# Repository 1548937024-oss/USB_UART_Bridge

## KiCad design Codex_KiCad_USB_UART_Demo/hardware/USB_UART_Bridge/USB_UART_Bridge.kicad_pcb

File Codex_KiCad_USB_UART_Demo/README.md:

# Codex + KiCad USB-UART 演示

本目录用于建立一套可复现的 Codex 驱动 PCB 开发流程。演示电路采用
`CH343G`，实现隔离型 USB 2.0 转 3.3 V UART。

整个流程把需求、设计意图、脚本和 KiCad 工程文件都作为可版本控制的
工程资料。允许使用图形界面完成必要操作，但每个发布关口都必须能够通过
命令行重复执行。

## 当前进度

- P0 环境锁定：已完成。
- P1 需求锁定：已完成。
- P2 架构与选型：已完成。
- P3 原理图：已完成 `rev 0.2`，采用 A4 层次化图纸，已按 §10 统一网络命名、增加模块边框、
  器件注释、修订表和 `TP1-TP4` 测试点；ERC 为 0 错误、0 警告，栅格、标签间距和
  A4 边界检查均已通过，已重新生成网表、BOM 和 PDF。
- P4 PCB 设置与布局：已完成初版布局，生成 55 x 32 mm、2 mm 圆角、2 层 PCB、
  37 个封装（含 4 个 M2 安装孔）和 2 个隔离禁布区；J1 位于最左侧，
  J2/JP1 使用 2.54 mm 卧式弯针，在最右侧上下并排并缩小间隙，连接器本体伸出板外；
  四个 M2 安装孔布置在板卡四角；
  PS1 的 1/2 脚与 3/4 脚分置隔离区两侧，中间设置槽；U2 紧邻 J1 放置。
- P5 布线：已完成脚本化布线，DRC 为 0 个未连接项；保留 4 条 J1
  封装内部孔间距错误和连接器有意伸出板边产生的丝印警告。

当前原理图的网络标签优先落在实际连接走线上，不再为每个引脚固定拉出
`7.62 mm` 引线。同一局部区域内的同网引脚使用短实线连接；跨区域或会形成
交叉的连接使用同名网络标签。器件按照 USB 输入、桥接、隔离和输出四个功能区
排列，并通过旋转调整电流方向和走线方向。

原理图中的器件原点、全部引脚位置、走线端点、网络标签和 no-connect 均
必须落在 KiCad 默认的 `1.27 mm` 栅格上。生成脚本和验证脚本都会执行该检查。

原理图分为三个层次：

- 顶层 `USB_UART_Bridge.kicad_sch`：放置 USB-C、USB ESD、CC 下拉、UART 接口和
  VOUT 选择，并连接外部电气网络；USB 功能块整体位于左下区域。
- `Power.kicad_sch`：放置保险丝、隔离电源、隔离侧 LDO 及其去耦。
- `Communicate.kicad_sch`：放置 USB-UART 桥、数字隔离器和辅助状态电路。

跨图纸信号使用层次标签和图纸引脚连接。电源网络使用 `power` 库中的电源符号，
不使用普通网络标签。

`PWR_FLAG` 用于告诉 ERC 某些电源或地网络由外部连接器直接提供，避免把
USB-C、排针等无源接口误报为“电源没有驱动源”。它不是电源器件，也不会改变
`PWR_5V_RAW`、`PWR_5V_USB`、`PWR_VOUT_ISO`、`GND` 之间的实际连接关系。

## 版本记录

| Rev | Date | Author | Changes |
| --- | --- | --- | --- |
| 0.2 | 2026-09-19 | Codex | 修复 ERC 告警和错误，收紧 `pin_to_pin` 与单端全局标签检查，修正标签间距和 A4 边界问题 |
| 0.1 | 2026-09-14 | Codex | 初始层次化隔离 USB-UART 原理图、ERC 与制造输出流程 |

## 采购与成本

- `procurement/USB_UART_Bridge_Procurement_BOM.xlsx`：采购 BOM、预算单价、询价输入、
  采购数量、备件率和成本汇总。
- `procurement/USB_UART_Bridge_Procurement_BOM.csv`：可导入采购系统或继续编辑的
  简化版 BOM。

当前成本表按 5 片首版样机、默认 10% 备件率估算。表中单价用于提前备料和数量级
评估，实际下单前应把供应商报价填入“实际报价”列，并复核库存、MOQ 和交期。

原理图使用工程内的 `AD_Style_A4.kicad_wks` 图纸模板。该模板采用 A4 横向
ISO 5457/ISO 7200 compact 分区边框和右下工程标题栏，整体观感接近 AD
原理图的工业图纸样式。KiCad 图形界面和 `kicad-cli` PDF 导出均引用同一模板。

非电源网络会按曼哈顿距离建立最小生成树，并自动选择尽量短的直角走线把同网
引脚实际连接起来；电源网络继续通过电源符号建立全局连接。

生成流程最后会调用 `kicad-cli sch upgrade --force`，确保三张原理图文件头
始终升级为当前安装的 KiCad 10.0 格式。

## 演示电路

### 主要器件

| 位号 | 器件 | 用途 |
| --- | --- | --- |
| J1 | USB-C 母座，USB 2.0 16P | USB 设备接口 |
| U1 | CH343G | USB 转 UART 桥接器，最高 6 Mbps |
| U2 | USBLC6-2SC6 | USB 数据线 ESD 保护 |
| U3 | ISO7721D | 双通道数字隔离器，100 Mbps |
| PS1 | IB0505LS-1WR3 | 5 V 输入、5 V 隔离输出电源，LS/SIP-4 封装 |
| U4 | AP2112K-3.3 | 隔离侧 3.3 V LDO |
| F1 | 0.5 A 自恢复保险丝 | VBUS 保护 |
| R1, R2 | 5.1 kOhm | USB-C USB_CC1/USB_CC2 下拉 |
| R4, R5 | 1 kOhm | 状态 LED 限流 |
| R6, R7 | 33 Ohm | TXD/RXD 串联端接 |
| D1, D2 | LED | 活动状态和电源指示 |
| C1 | 4.7 uF | USB 侧电源体去耦 |
| C2-C5 | 100 nF | V3/VIO 高频去耦 |
| C6 | 10 uF | V3/VIO 体去耦 |
| C7-C8 | 10 uF | 隔离电源输入、输出去耦 |
| C9 | 100 nF | 3V3_ISO 高频去耦 |
| C10 | 10 uF | 3V3_ISO 体去耦 |
| C11 | 100 nF | U3 隔离侧高频去耦 |
| C12 | 10 uF | U3 隔离侧体去耦 |
| J2 | 1x4，2.54 mm 卧式弯针 | GND、VOUT、RXD、TXD，从板卡右侧水平出线 |
| JP1 | 1x3，2.54 mm 卧式弯针 | 隔离侧 VOUT 的 3V3/5V 选择，从板卡右侧水平出线 |
| TP1 | 1.0 mm 测试点 | USB 侧 5 V：`5 V +/-5%` |
| TP2 | 1.0 mm 测试点 | 隔离 3.3 V：`3.3 V +/-5%` |
| TP3, TP4 | 1.0 mm 测试点 | 隔离 UART TX/RX：`3.3 V logic, <=5 Mbps` |
| H1-H4 | M2 安装孔 | 机械固定 |

### 电源域

- `PWR_5V_RAW`：USB-C VBUS。
- `PWR_5V_USB`：经过保险丝和 ESD 保护后的 USB 侧 5 V。
- `PWR_3V3_USB`：CH343G 的 V3 输出，用于 USB 侧逻辑和隔离器侧 1。
- `PWR_5V_ISO`：`IB0505LS-1WR3` 产生的隔离 5 V 电源。
- `PWR_3V3_ISO`：`AP2112K-3.3` 从隔离 5 V 产生的隔离 3.3 V 电源。
- `PWR_VOUT_ISO`：J2 第 2 脚的隔离输出，可通过 JP1 选择 `PWR_3V3_ISO` 或 `PWR_5V_ISO`。
- `GND`：USB 侧地。
- `ISO_GND`：隔离侧地。

JP1 的连接关系如下：

| JP1 引脚 | 网络 | 说明 |
| --- | --- | --- |
| 1 | `PWR_5V_ISO` | 选择隔离 5 V 输出 |
| 2 | `PWR_VOUT_ISO` | 连接到 J2 第 2 脚 |
| 3 | `PWR_3V3_ISO` | 选择隔离 3.3 V 输出 |

默认建议安装跳线帽将 JP1 的 2-3 脚短接，即输出 `PWR_3V3_ISO`。选择 `PWR_5V_ISO`
时，输出来自隔离电源模块。两个输出都在隔离侧，不能与 USB 侧地直接连接。

`Power` 图纸中的 `C7`、`C8` 分别与 `PS1` 的输入、输出引脚重合放置，
`C9` 与 `U4.5` 重合放置，`C10` 通过 `2.54 mm` 短线就近接到 `U4.5`。
`Communicate` 图纸中的 `D2` 旋转 `180°`，与横放的 `R5` 组成从左到右的
指示灯电流路径；`R6`、`R7` 也采用横放方向以缩短 UART 走线。

原理图按照 `AGENTS.md` 的 §10 可读性规范增加了模块边框、型号/参数/封装注释、
首页电源流向和修订表。页间信号只使用层次端口；电源和地使用统一网络符号。

该选择只改变 J2 第 2 脚的 `PWR_VOUT_ISO`，不会改变 TXD、RXD 的
3.3 V 逻辑电平。如果目标设备需要 5 V UART 逻辑，必须增加电平转换电路。

### 隔离架构

- 隔离栅位于 CH343G 与外部 UART 接口之间。
- `CH343G` 的最高 UART 数据率为 6 Mbps，满足 5 Mbps 以上要求。
- `U3 ISO7721D` 隔离 TXD 和 RXD，通道方向为一路输出和一路输入。
- `ISO7721D` 的最高数据率为 100 Mbps，远高于 UART 5 Mbps 的要求。
- `PS1 IB0505LS-1WR3` 提供 1 W 隔离电源，输入为 USB 侧 5 V，输出为隔离 5 V。
- `U4 AP2112K-3.3` 从隔离 5 V 产生隔离 3.3 V，为隔离器和外部接口供电。
- `GND` 与 `ISO_GND` 必须分开铺铜，隔离带内不得有铜皮、走线或过孔跨越。
- 隔离器件下方设置大于等于 5 mm 的爬电距离，并在装配图中标注隔离带。
- 建议在隔离带设置板边开槽，以提高爬电距离和隔离可靠性。
- 演示板隔离目标为 1.5 kVrms，生产前必须按最终安全等级完成耐压测试。

隔离输出负载按 `100 mA` 设计。`IB0505LS-1WR3` 和 `AP2112K-3.3` 都能覆盖
该电流，但不能把 USB 侧的 5 V 或 3.3 V 与隔离侧地直接连接。

USB 数据线没有经过数字隔离器，因为 CH343G 位于 USB 侧，隔离栅在其之后。
如果 USB D+/D- 也必须隔离，则需要改用 `ADuM3160` 或 `ADuM4160` 等 USB
隔离器，整体电源和信号架构需要重新设计。

当前桥接器上限为 6 Mbps。如果后续要求 10 Mbps 或 12 Mbps，可将 CH343G
替换为 `FT232H` 或 `FT2232H`，同时重新审核 USB、时钟、EEPROM 和隔离器功耗。

### UART 接口

| J2 引脚 | 信号 | 板卡侧方向 |
| --- | --- | --- |
| 1 | GND | 电源 |
| 2 | PWR_VOUT_ISO | 隔离 3V3/5V 参考电源输出 |
| 3 | RXD | 板卡输入 |
| 4 | TXD | 板卡输出 |

UART 网络按信号方向命名：

| 网络 | 含义 |
| --- | --- |
| `UART_TX_BRIDGE` | CH343G 的 UART TX 输出 |
| `UART_TX_ISO_IN` | 数字隔离器侧 1 输入 |
| `UART_TX_ISO_OUT` | 隔离后的 TXD 输出 |
| `UART_RX_ISO_IN` | 隔离侧 RXD 输入 |
| `UART_RX_ISO_OUT` | 数字隔离器侧 2 输入 |
| `UART_RX_BRIDGE` | 返回 CH343G 的 UART RX 输入 |

## 开发流程

### P0. 环境锁定

输入：

- KiCad 版本。
- Python 和 `pcbnew` 版本。
- 符号库和封装库位置。

Codex 操作：

- 自动检测当前 KiCad 安装位置，不写死安装路径。
- 验证 `kicad-cli`、`pcbnew`、符号库和封装库。
- 在工程日志中记录实际环境。

通过条件：

- `kicad-cli --version` 执行成功。
- `import pcbnew` 执行成功。
- 所需符号和封装全部能够解析。

### P1. 需求锁定

当前需求基线位于 `requirements.yaml`，使用 `FR`、`ER`、`ME`、`PCB`、`VER`
编号，并为每项记录优先级、验收条件、验证方法和发布关口。器件与工艺选型
作为冻结设计约束单独管理，不再和功能需求混写。

输入：

- 电气接口和电压等级。
- 板卡尺寸、连接器方向和安装约束。
- 制造工艺和设计规则假设。

Codex 操作：

- 将需求转换为可测试的验收条件。
- 标出尚未确认的电气或机械假设。
- 将需求和实现细节分开管理。

通过条件：

- 每项需求都有可测量的验收条件。
- 不存在隐含的安全或接口假设。

### P2. 架构与选型

输入：

- 已确认的需求基线。
- 器件供货、封装、生命周期和成本约束。

Codex 操作：

- 选择总体架构和核心芯片。
- 建立器件与网络设计意图。
- 在绘制原理图之前检查符号和封装是否可用。
- 确认隔离电压、爬电距离、数据率和隔离侧供电能力。

通过条件：

- 每个器件都有制造商料号和封装。
- 电源、复位、时钟、USB 和 UART 拓扑已经记录。
- 隔离器数据率、隔离电源功率和隔离电压满足需求。
- 未使用引脚和启动配置引脚已经明确处理。

### P3. 原理图

输入：

- `requirements.yaml`。
- `design_intent.yaml`。

Codex 操作：

- 创建或修改 KiCad 原理图。
- 保持网络名称稳定且便于脚本处理。
- 通过 KiCad 生成网表和 BOM，不以手工表格代替。

通过条件：

```powershell
kicad-cli sch erc --format json --severity-all --exit-code-violations `
  -o reports/erc.json USB_UART_Bridge.kicad_sch

kicad-cli sch export netlist `
  -o generated/USB_UART_Bridge.net USB_UART_Bridge.kicad_sch
```

- ERC 未排除错误数为 0。
- 网表生成成功。
- BOM 与原理图中的位号、参数和封装一致。

### P4. PCB 设置与布局

当前工程已提供 `scripts/generate_pcb.py`，布局数据来自
`design_intent.yaml` 的 `pcb_layout` 段。生成结果包括板框、安装孔、网络分配、
器件摆放、隔离带禁布区和基础设计规则。

制造和载流规范源为 `pcb_design_rules.yaml`，工程说明和未关闭项见
`docs/PCB_Design_Spec.md`。制造能力参考嘉立创公开工艺，载流与回流依据
IPC-2152 和 IPC-2221B 建立项目级设计目标。

生成命令：

```powershell
D:\KiCad10.0\bin\python.exe .\scripts\generate_pcb.py
```

输入：

- 网表。
- 板框和机械约束。
- 叠层、网络类和制造限制。

Codex 操作：

- 从已审核工程创建 PCB。
- 分配封装并同步网络。
- 根据机械边界放置连接器。
- 缩短 USB 差分对，并远离噪声节点。
- 将去耦电容放置在对应电源引脚附近。
- 在 PCB 上明确划分 USB 侧和隔离侧，禁止跨越隔离带布线。

通过条件：

- 板框与机械图一致。
- 所有封装都有有效 courtyard。
- USB、电源、UART、复位和 LED 网络连接正确。
- 连接器与安装孔不存在碰撞。
- 隔离带、爬电距离和开槽位置满足设计规则。

当前布局检查记录：

- 器件不越出板框，例外仅为 J1、J2、JP1 的机械或插拔部分。
- PCB 在最终输出中整体居中于 A4 图框，板内器件和机械结构的相对坐标不变。
- 器件物理外框无重叠；隔离器 `U3` 和隔离电源 `PS1` 跨隔离带，其他器件和铜结构不跨带。
- J2/JP1 顺时针旋转 90°，在最右侧上下并排，引脚朝板外，便于安装杜邦线。
- 4 个 M2 安装孔靠近板卡四角放置；左侧 J1 与 H1/H3 两个角孔同时存在且无 courtyard 重叠。
- PS1 第 1/2 脚位于 USB 侧，第 3/4 脚位于隔离侧，中间设置实际板槽；
  LS/SIP-4 封装将第 2/3 脚间距扩大到 `7.62 mm`，满足 `1.0 mm` 非金属槽要求。
- U2 紧邻 J1，用于优先缩短 USB D+/D- 的 ESD 泄放路径。
- J1 使用可加载的近似 3D 模型进行机械检查；机械发布前需替换为 XKB 官方 STEP
  或确认等效模型。
- PS1 已导入缩放后的近似 SIP-4 STEP 模型，机械发布前需替换为 YLPTEC 官方
  STEP 或完成尺寸等效性确认。
- 布线完成后 DRC 未连接项为 0；剩余 12 条固定项为 4 条 J1 封装内部孔间距和
  8 条 J2/JP1 伸出板边的丝印警告。
- USB-C 标准封装内部存在 4 个 NPTH 到 `GND` 焊盘 `A1/B12`、`A12/B1`
  的 0.1847 mm 间距检查项，低于当前板级 0.25 mm 配置，差 0.0653 mm；
  该项仍待板厂 DFM 或封装修改确认，不能视为已批准例外。
- 当前布局 DRC 除上述 4 个封装内部间距错误外，另有 8 条丝印边界警告，
  来源是 J2/JP1 为便于插拔而刻意伸出板外；无 courtyard 重叠。

### P5. 布线

当前工程已提供 `scripts/route_pcb.py`，默认复用冻结的 Specctra SES 基线
`generated/routing/USB_UART_Bridge_frozen.ses`，避免 FreeRouting 全局策略在
相同输入下产生随机结果。基线哈希为：

```text
AA3BCD88D0543DB050E312FE63A81F5840888BC9388077DFE603535D5AF3846E
```

生成命令：

```powershell
D:\KiCad10.0\bin\python.exe .\scripts\route_pcb.py
```

脚本会重建布局、导入冻结基线、把低于项目下限的走线统一到 `0.20 mm`，
补通 `PWR_VOUT_ISO` 和 `PWR_3V3_USB`，再铺设 `GND`、`ISO_GND` 和局部
`PWR_5V_ISO` 铜皮。若需要重新自动布线，先删除冻结 SES 文件，再运行同一脚本。

输入：

- 已完成布局的 PCB。
- 网络类和布线约束。

Codex 操作：

- 优先处理电源和地。
- 将 USB D+/D- 作为短差分对布线，并保证参考平面连续。
- 处理 UART 和低速控制信号。
- 使用 GND 铜皮，并检查过孔缝合。
- 通过脚本处理重复工作，关键高速决策仍保留人工审核。

通过条件：

- 不存在未布线连接。
- USB 差分对长度偏差满足工程限制。
- 电源和地回流路径连续。
- 不存在锐角走线或不必要的残桩。
- TXD 和 RXD 全部通过隔离器，未出现直连旁路。
- 5 Mbps UART 回环测试无误码，示波器测量波形无明显振铃。

### P6. 验证

输入：

- 已完成的 PCB。
- 原理图网表和设计规则。

Codex 操作：

- 运行带原理图一致性检查的 DRC。
- 重新填充铜皮并再次运行 DRC。
- 生成 3D 渲染并检查机械配合。
- 审核报告并修复问题，不以屏蔽方式绕过问题。

通过条件：

```powershell
kicad-cli pcb drc --schematic-parity --refill-zones --save-board `
  --format json --severity-all --exit-code-violations `
  -o reports/drc.json USB_UART_Bridge.kicad_pcb
```

- 未排除 DRC 错误数为 0。
- 原理图与 PCB 不存在一致性差异。
- 铜皮填充为最新状态。
- 渲染结果符合装配方向要求。
- `GND` 与 `ISO_GND` 不存在短路，隔离耐压测试满足设计要求。

### P7. 制造输出

输入：

- 已审核的 PCB 和制造工艺。

Codex 操作：

- 生成 Gerber、钻孔、坐标和装配资料。
- 生成用于机械集成的 STEP 文件。
- 归档发布时使用的全部设置和报告。

通过条件：

- Gerber 和钻孔层完整。
- Gerber 查看器能够正确打开钻孔和板框。
- Gerber 与源文件版本可以追溯。
- 从干净目录可以重新生成发布包。

### P8. 发布与变更控制

输入：

- 制造包。
- 测试结果和已知限制。

Codex 操作：

- 冻结版本。
- 记录 ERC、DRC 结果和生成文件哈希。
- 下一版本只能从已发布基线继续修改。

通过条件：

- 源文件、报告和制造输出一起提交。
- 干净环境下可以复现相同发布文件。
- 任何人工修正都记录在变更说明中。

## 实现方法

推荐采用三层结构：

1. **人工审核的源数据**：需求、框图、关键器件、叠层和机械约束。
2. **Codex 辅助的设计操作**：网表/BOM 生成、封装分配、布局辅助、
   重复布线、检查和导出。
3. **KiCad 验证**：ERC、DRC、原理图一致性、铜皮重填、3D 渲染、
   Gerber 和 STEP 导出。

完全自动的器件选型和全自动布线不作为发布关口。它们可以生成初始方案，
但正式设计仍然需要电气、机械、EMC、热设计和制造审核。

## 项目关口汇总

| 关口 | 必须达到的结果 |
| --- | --- |
| G0 环境 | `kicad-cli` 和 `pcbnew` 可用 |
| G1 需求 | 可测试且无歧义 |
| G2 架构 | 器件、封装、电源和复位已验证 |
| G3 原理图 | ERC 通过并成功生成网表 |
| G4 布局 | 机械配合和去耦位置已验证 |
| G5 布线 | 连接关系和受控布线已验证 |
| G6 DRC | DRC 和原理图一致性全部通过 |
| G6.1 隔离 | 电源、地和四路串口信号均已隔离 |
| G6.2 速率 | 5 Mbps UART 回环无误码 |
| G7 制造 | Gerber、钻孔、坐标和 STEP 完整 |
| G8 发布 | 可复现且可追溯 |

## 工程目录

```text
Codex_KiCad_USB_UART_Demo/
  README.md
  requirements.yaml
  design_intent.yaml
  scripts/
    validate.ps1
  hardware/
    USB_UART_Bridge/
      USB_UART_Bridge.kicad_sch
      Power.kicad_sch
      Communicate.kicad_sch
  generated/
  reports/
  manufacturing/
```

`hardware/` 在初始化 KiCad 工程时创建。`generated/`、`reports/` 和
`manufacturing/` 都是可重新生成的输出目录。

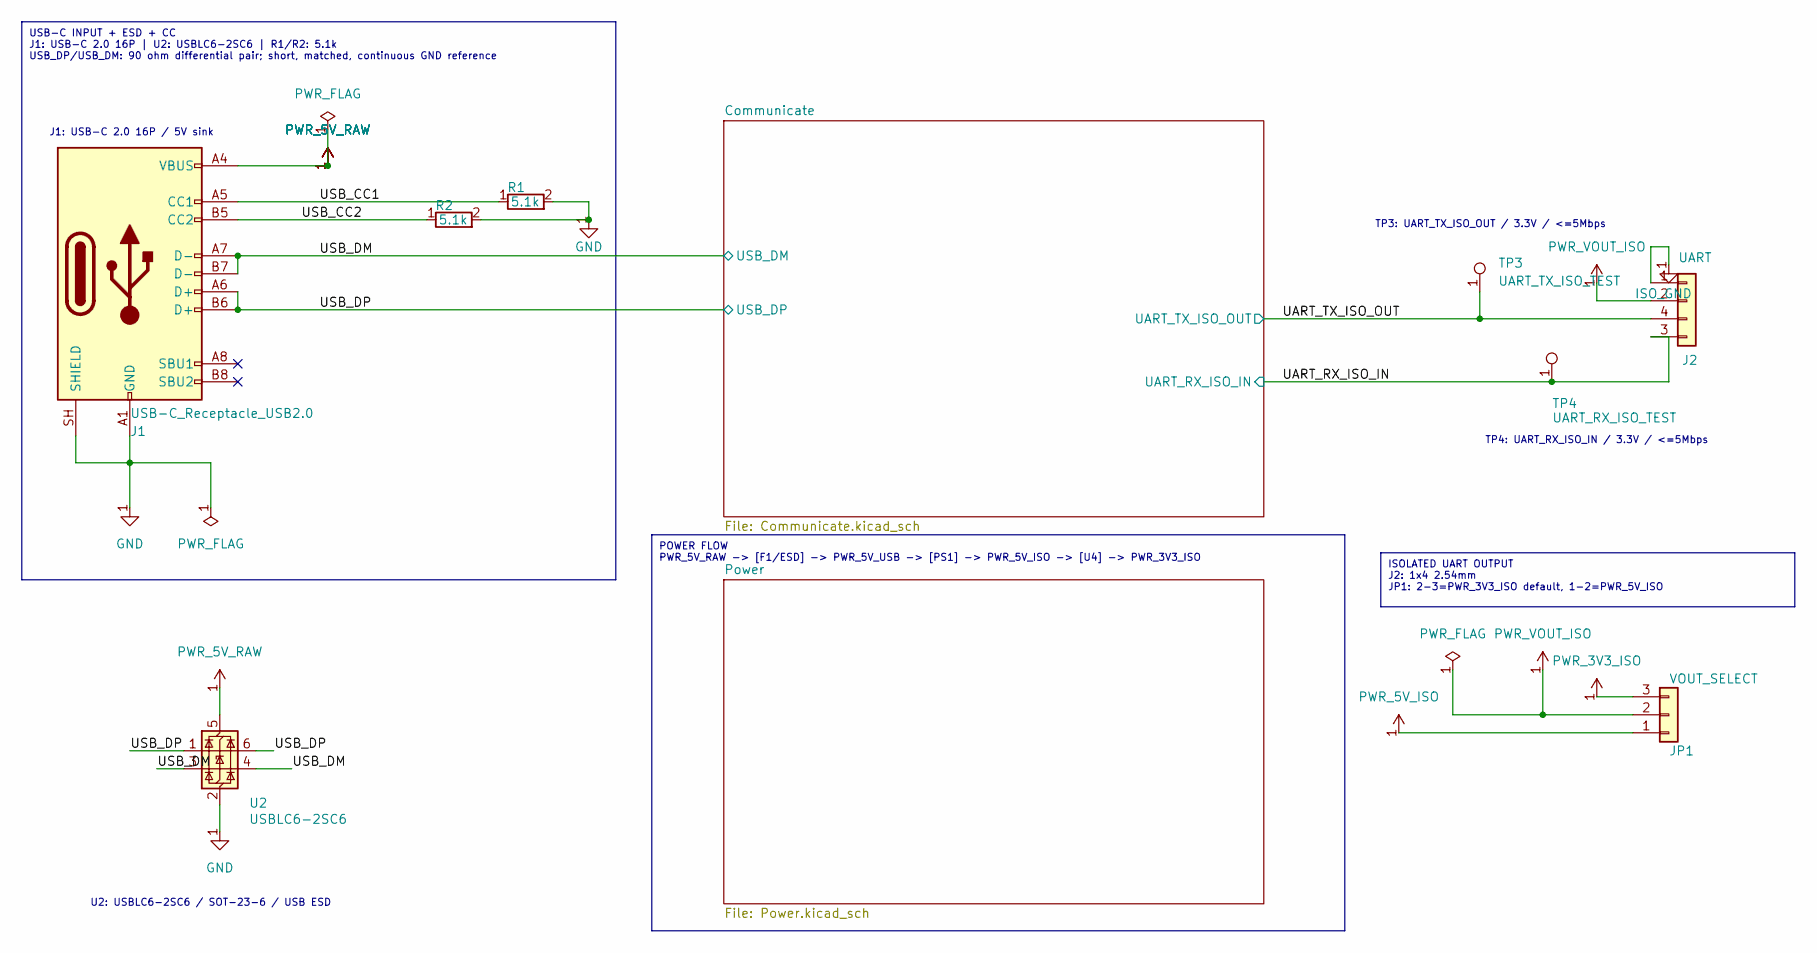
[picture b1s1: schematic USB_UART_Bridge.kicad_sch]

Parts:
J1: USB-C_Receptacle_USB2.0; USB_C_Receptacle_XKB_U262-16XN-4BVC11
J2: UART; PinHeader_1x04_P2.54mm_Vertical
JP1: VOUT_SELECT; PinHeader_1x03_P2.54mm_Vertical
R1, R2: 5.1k; R_0402_1005Metric
TP3: UART_TX_ISO_TEST; TestPoint_Pad_D1.0mm
TP4: UART_RX_ISO_TEST; TestPoint_Pad_D1.0mm
U2: USBLC6-2SC6; SOT-23-6

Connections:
/UART_RX_ISO_IN: J2.3, TP4.1; also elsewhere on the board
/UART_TX_ISO_OUT: J2.4, TP3.1; also elsewhere on the board
/USB_CC1: J1.A5 (CC1), R1.1
/USB_CC2: J1.B5 (CC2), R2.1
/USB_DM: J1.A7 (D-), J1.B7 (D-), U2.3 (I/O2), U2.4 (I/O2); also elsewhere on the board
/USB_DP: J1.A6 (D+), J1.B6 (D+), U2.1 (I/O1), U2.6 (I/O1); also elsewhere on the board
GND: J1.A1 (GND), J1.A12 (GND), J1.B1 (GND), J1.B12 (GND), J1.SH (SHIELD), R1.2, R2.2, U2.2 (GND); also elsewhere on the board
ISO_GND: J2.1; also elsewhere on the board
PWR_3V3_ISO: JP1.3; also elsewhere on the board
PWR_5V_ISO: JP1.1; also elsewhere on the board
PWR_5V_RAW: J1.A4 (VBUS), J1.A9 (VBUS), J1.B4 (VBUS), J1.B9 (VBUS), U2.5 (VBUS); also elsewhere on the board
PWR_VOUT_ISO: J2.2, JP1.2

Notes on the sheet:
TP3: UART_TX_ISO_OUT / 3.3V / <=5Mbps
J1: USB-C 2.0 16P / 5V sink
U2: USBLC6-2SC6 / SOT-23-6 / USB ESD
TP4: UART_RX_ISO_IN / 3.3V / <=5Mbps
ISOLATED UART OUTPUT J2: 1x4 2.54mm JP1: 2-3=PWR_3V3_ISO default, 1-2=PWR_5V_ISO
USB-C INPUT + ESD + CC J1: USB-C 2.0 16P | U2: USBLC6-2SC6 | R1/R2: 5.1k USB_DP/USB_DM: 90 ohm differential pair; short, matched, continuous GND reference
POWER FLOW PWR_5V_RAW -> [F1/ESD] -> PWR_5V_USB -> [PS1] -> PWR_5V_ISO -> [U4] -> PWR_3V3_ISO

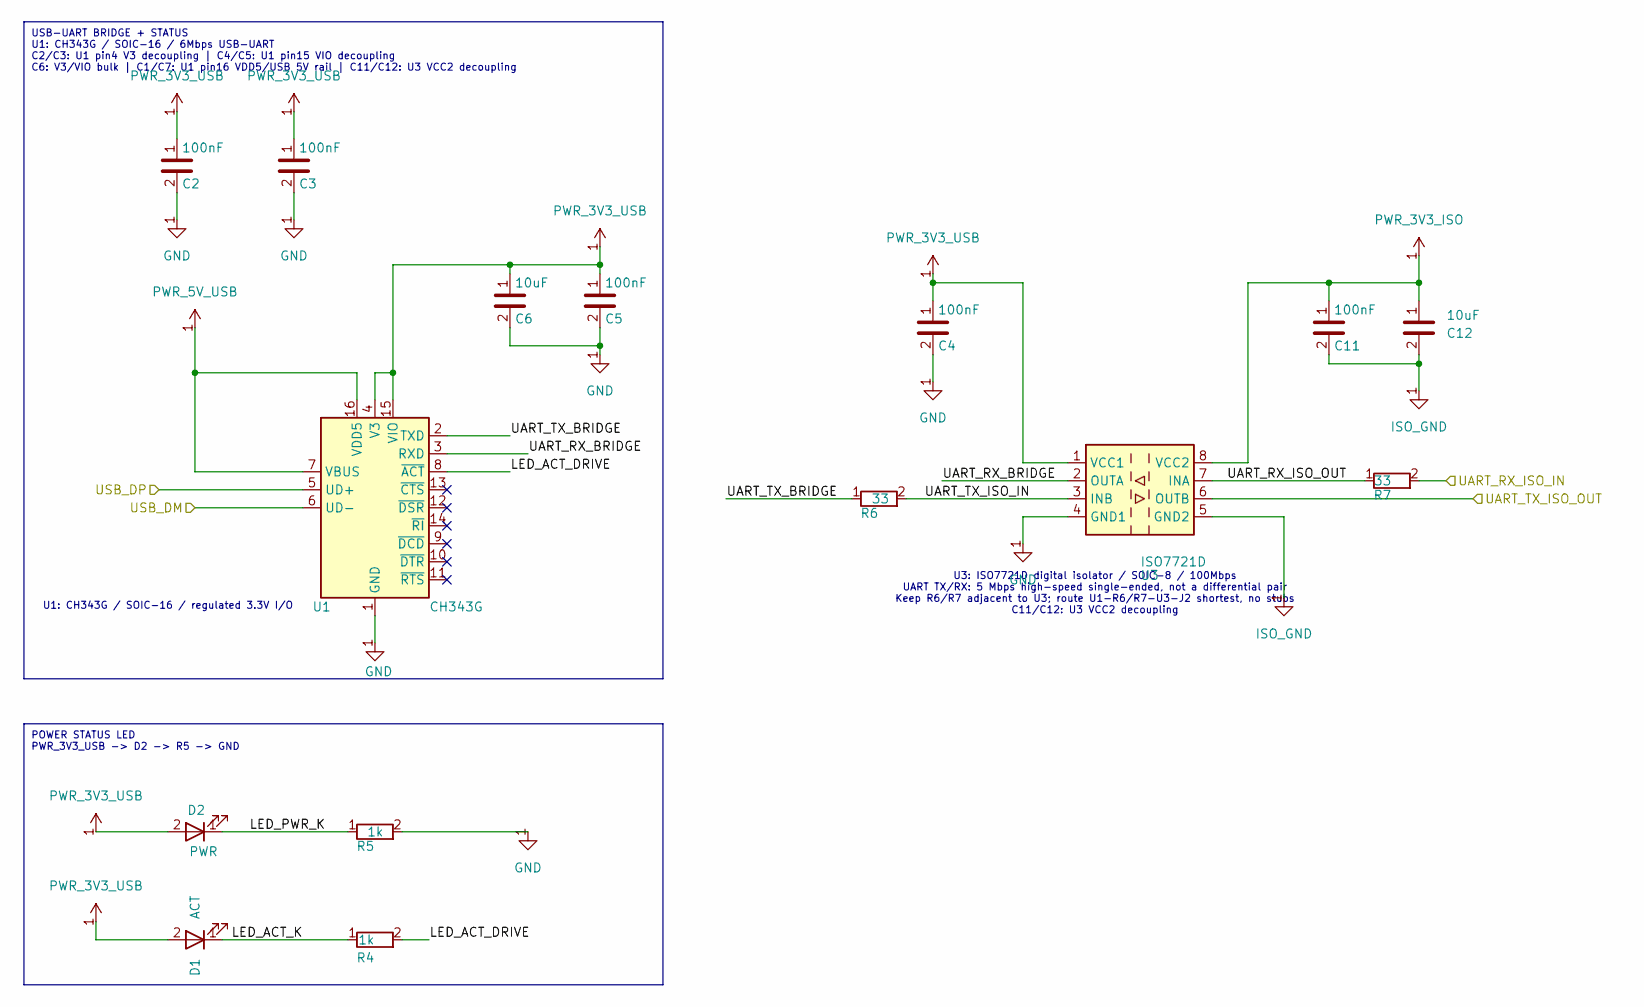
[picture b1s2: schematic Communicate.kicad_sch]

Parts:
C2, C3, C4, C5: 100nF; C_0402_1005Metric
C6, C12: 10uF; C_0603_1608Metric
C11: 100nF; C_0603_1608Metric
D1: ACT; LED_0603_1608Metric
D2: PWR; LED_0603_1608Metric
R4, R5: 1k; R_0402_1005Metric
R6, R7: 33; R_0402_1005Metric
U1: CH343G; SOIC-16_3.9x9.9mm_P1.27mm
U3: ISO7721D; SOIC-8_3.9x4.9mm_P1.27mm

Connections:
/Communicate/LED_ACT_DRIVE: R4.2, U1.8 (~ACT)
/Communicate/LED_ACT_K: D1.1 (K), R4.1
/Communicate/LED_PWR_K: D2.1 (K), R5.1
/Communicate/UART_RX_BRIDGE: U1.3 (RXD), U3.2 (OUTA)
/Communicate/UART_RX_ISO_OUT: R7.1, U3.7 (INA)
/Communicate/UART_TX_BRIDGE: R6.1, U1.2 (TXD)
/Communicate/UART_TX_ISO_IN: R6.2, U3.3 (INB)
/UART_RX_ISO_IN: R7.2; also elsewhere on the board
/UART_TX_ISO_OUT: U3.6 (OUTB); also elsewhere on the board
/USB_DM: U1.6 (UD-); also elsewhere on the board
/USB_DP: U1.5 (UD+); also elsewhere on the board
GND: C2.2, C3.2, C4.2, C5.2, C6.2, R5.2, U1.1 (GND), U3.4 (GND1); also elsewhere on the board
ISO_GND: C11.2, C12.2, U3.5 (GND2); also elsewhere on the board
PWR_3V3_ISO: C11.1, C12.1, U3.8 (VCC2); also elsewhere on the board
PWR_3V3_USB: C2.1, C3.1, C4.1, C5.1, C6.1, D1.2 (A), D2.2 (A), U1.4 (V3), U1.15 (VIO), U3.1 (VCC1)
PWR_5V_USB: U1.7 (VBUS), U1.16 (VDD5); also elsewhere on the board

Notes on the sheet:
U1: CH343G / SOIC-16 / regulated 3.3V I/O
U3: ISO7721D digital isolator / SOIC-8 / 100Mbps UART TX/RX: 5 Mbps high-speed single-ended, not a differential pair Keep R6/R7 adjacent to U3; route U1-R6/R7-U3-J2 shortest, no stubs C11/C12: U3 VCC2 decoupling
USB-UART BRIDGE + STATUS U1: CH343G / SOIC-16 / 6Mbps USB-UART C2/C3: U1 pin4 V3 decoupling | C4/C5: U1 pin15 VIO decoupling C6: V3/VIO bulk | C1/C7: U1 pin16 VDD5/USB 5V rail | C11/C12: U3 VCC2 decoupling
POWER STATUS LED PWR_3V3_USB -> D2 -> R5 -> GND

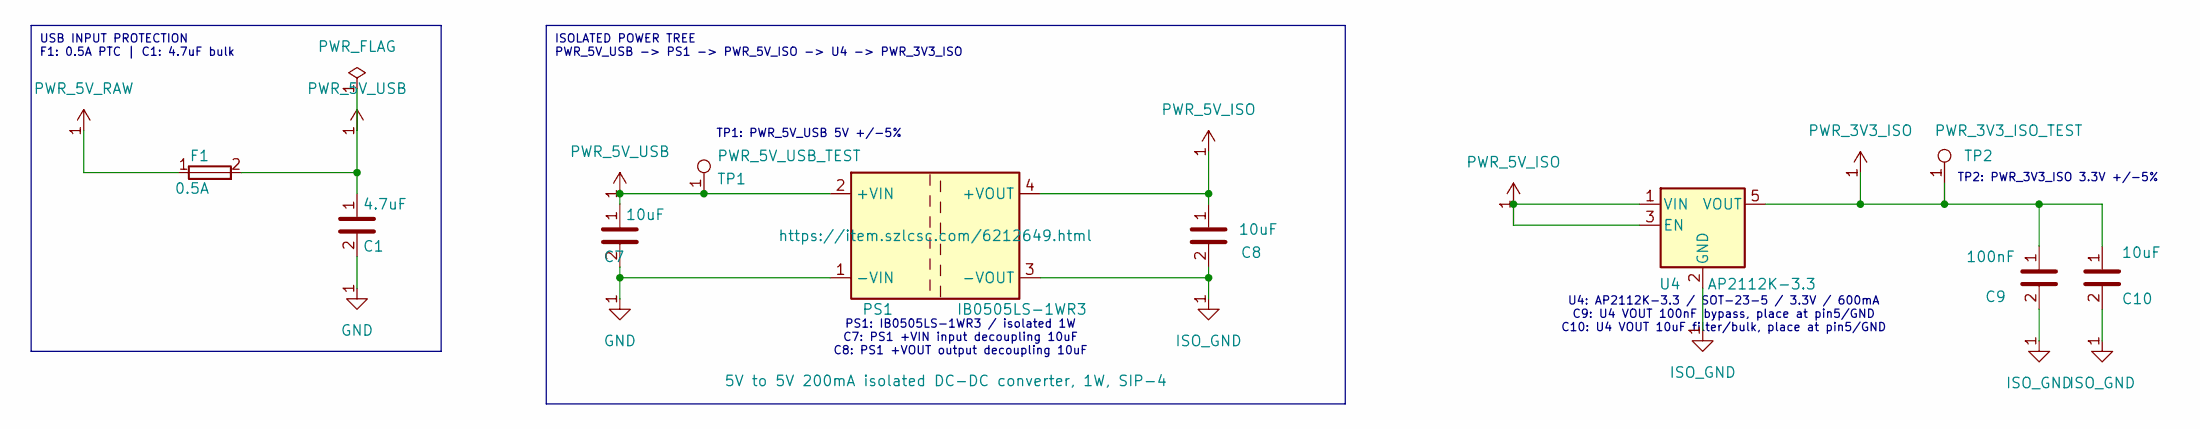
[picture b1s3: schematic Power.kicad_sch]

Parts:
C1: 4.7uF; C_0805_2012Metric
C7, C8: 10uF; C_1206_3216Metric
C9: 100nF; C_0603_1608Metric
C10: 10uF; C_0603_1608Metric
F1: 0.5A; Fuse_1206_3216Metric
PS1: IB0505LS-1WR3; Converter_DCDC_YLPTEC_IB0505LS-1WR3
TP1: PWR_5V_USB_TEST; TestPoint_Pad_D1.0mm
TP2: PWR_3V3_ISO_TEST; TestPoint_Pad_D1.0mm
U4: AP2112K-3.3; SOT-23-5

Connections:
GND: C1.2, C7.2, PS1.1 (-VIN); also elsewhere on the board
ISO_GND: C8.2, C9.2, C10.2, PS1.3 (-VOUT), U4.2 (GND); also elsewhere on the board
PWR_3V3_ISO: C9.1, C10.1, TP2.1, U4.5 (VOUT); also elsewhere on the board
PWR_5V_ISO: C8.1, PS1.4 (+VOUT), U4.1 (VIN), U4.3 (EN); also elsewhere on the board
PWR_5V_RAW: F1.1; also elsewhere on the board
PWR_5V_USB: C1.1, C7.1, F1.2, PS1.2 (+VIN), TP1.1; also elsewhere on the board

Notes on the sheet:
U4: AP2112K-3.3 / SOT-23-5 / 3.3V / 600mA C9: U4 VOUT 100nF bypass, place at pin5/GND C10: U4 VOUT 10uF filter/bulk, place at pin5/GND
PS1: IB0505LS-1WR3 / isolated 1W C7: PS1 +VIN input decoupling 10uF C8: PS1 +VOUT output decoupling 10uF
TP2: PWR_3V3_ISO 3.3V +/-5%
TP1: PWR_5V_USB 5V +/-5%
USB INPUT PROTECTION F1: 0.5A PTC | C1: 4.7uF bulk
ISOLATED POWER TREE PWR_5V_USB -> PS1 -> PWR_5V_ISO -> U4 -> PWR_3V3_ISO

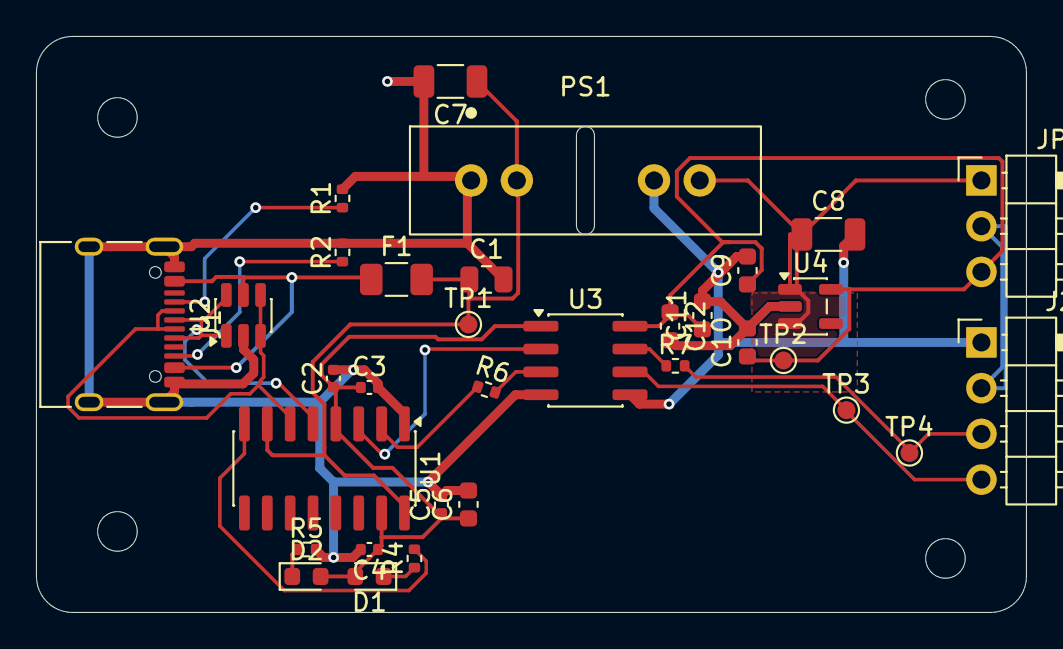
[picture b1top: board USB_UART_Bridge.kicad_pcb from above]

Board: 2 copper layers, 55.0 x 32.0 mm, 37 parts (0 on the bottom side), 21 nets.

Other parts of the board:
H1, H2, H3, H4: M2; MountingHole_2.2mm_M2

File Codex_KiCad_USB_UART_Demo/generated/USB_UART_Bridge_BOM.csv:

"Refs","Value","Footprint","Qty","DNP"
"C1","4.7uF","Capacitor_SMD:C_0805_2012Metric","1",""
"C2-C5","100nF","Capacitor_SMD:C_0402_1005Metric","4",""
"C6,C10,C12","10uF","Capacitor_SMD:C_0603_1608Metric","3",""
"C7,C8","10uF","Capacitor_SMD:C_1206_3216Metric","2",""
"C9,C11","100nF","Capacitor_SMD:C_0603_1608Metric","2",""
"D1","ACT","LED_SMD:LED_0603_1608Metric","1",""
"D2","PWR","LED_SMD:LED_0603_1608Metric","1",""
"F1","0.5A","Fuse:Fuse_1206_3216Metric","1",""
"J1","USB-C_Receptacle_USB2.0","Connector_USB:USB_C_Receptacle_XKB_U262-16XN-4BVC11","1",""
"J2","UART","Connector_PinHeader_2.54mm:PinHeader_1x04_P2.54mm_Vertical","1",""
"JP1","VOUT_SELECT","Connector_PinHeader_2.54mm:PinHeader_1x03_P2.54mm_Vertical","1",""
"PS1","CRE1S0505SC","Converter_DCDC:Converter_DCDC_Murata_CRE1xxxxxxSC_THT","1",""
"R1,R2","5.1k","Resistor_SMD:R_0402_1005Metric","2",""
"R4,R5","1k","Resistor_SMD:R_0402_1005Metric","2",""
"R6,R7","33","Resistor_SMD:R_0402_1005Metric","2",""
"TP1","PWR_5V_USB_TEST","TestPoint:TestPoint_Pad_D1.0mm","1",""
"TP2","PWR_3V3_ISO_TEST","TestPoint:TestPoint_Pad_D1.0mm","1",""
"TP3","UART_TX_ISO_TEST","TestPoint:TestPoint_Pad_D1.0mm","1",""
"TP4","UART_RX_ISO_TEST","TestPoint:TestPoint_Pad_D1.0mm","1",""
"U1","CH343G","Package_SO:SOIC-16_3.9x9.9mm_P1.27mm","1",""
"U2","USBLC6-2SC6","Package_TO_SOT_SMD:SOT-23-6","1",""
"U3","ISO7721D","Package_SO:SOIC-8_3.9x4.9mm_P1.27mm","1",""
"U4","AP2112K-3.3","Package_TO_SOT_SMD:SOT-23-5","1",""

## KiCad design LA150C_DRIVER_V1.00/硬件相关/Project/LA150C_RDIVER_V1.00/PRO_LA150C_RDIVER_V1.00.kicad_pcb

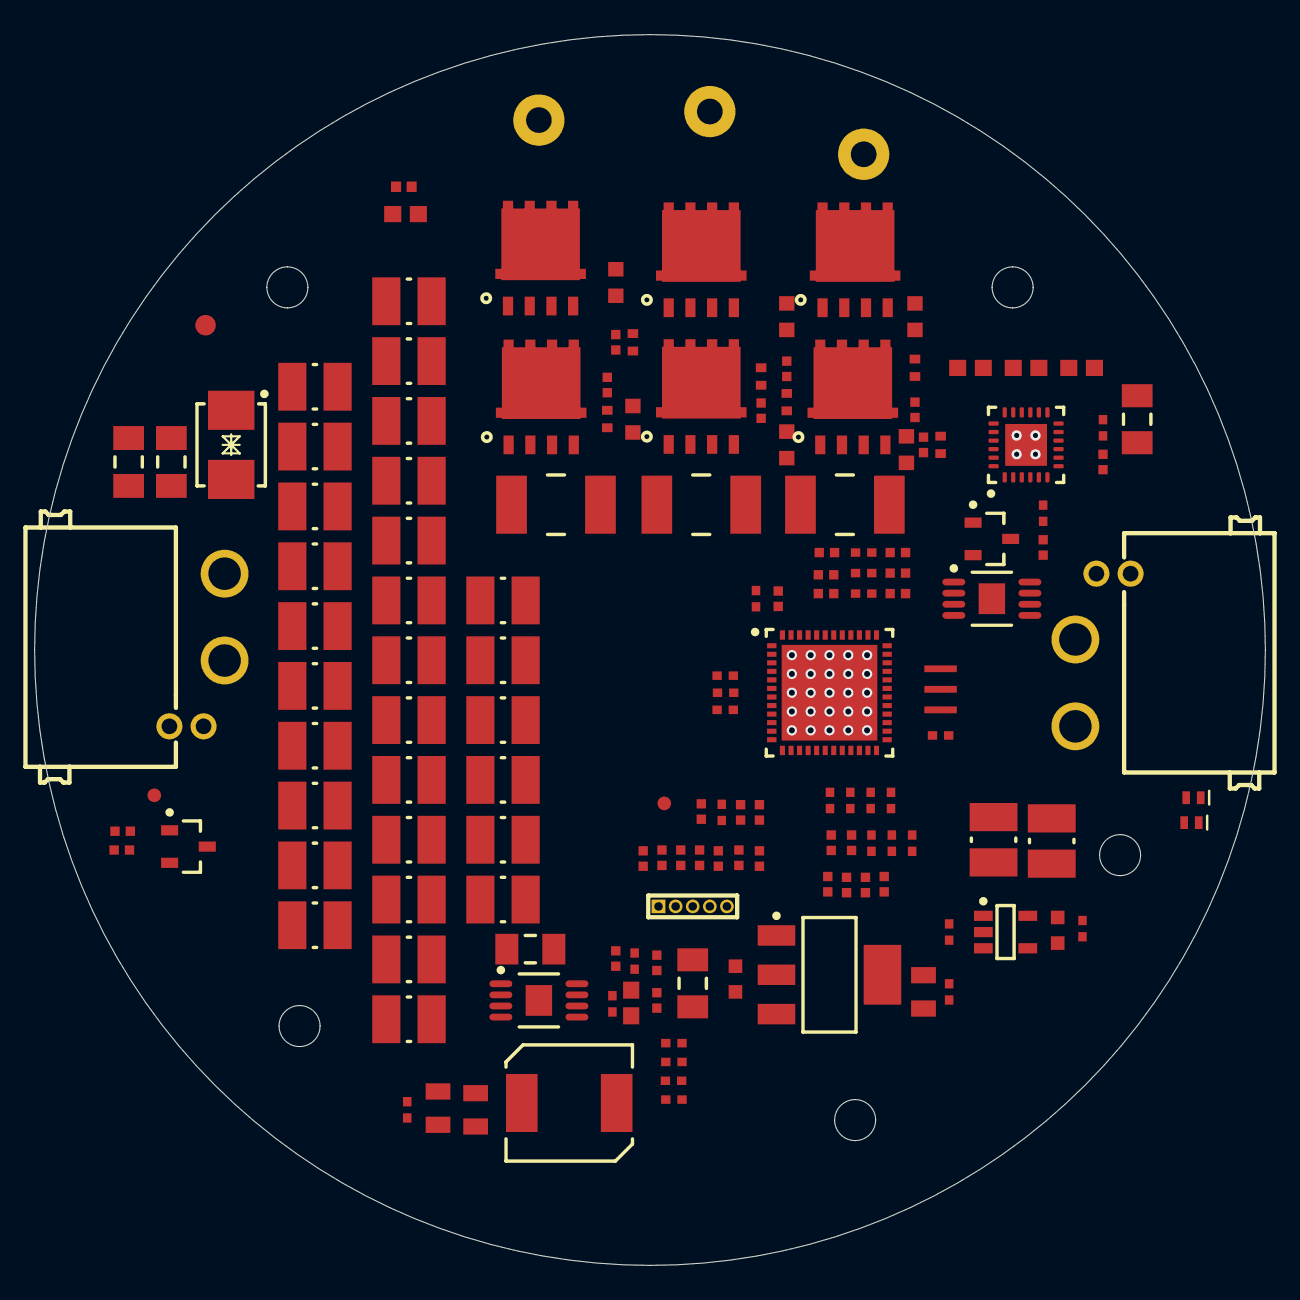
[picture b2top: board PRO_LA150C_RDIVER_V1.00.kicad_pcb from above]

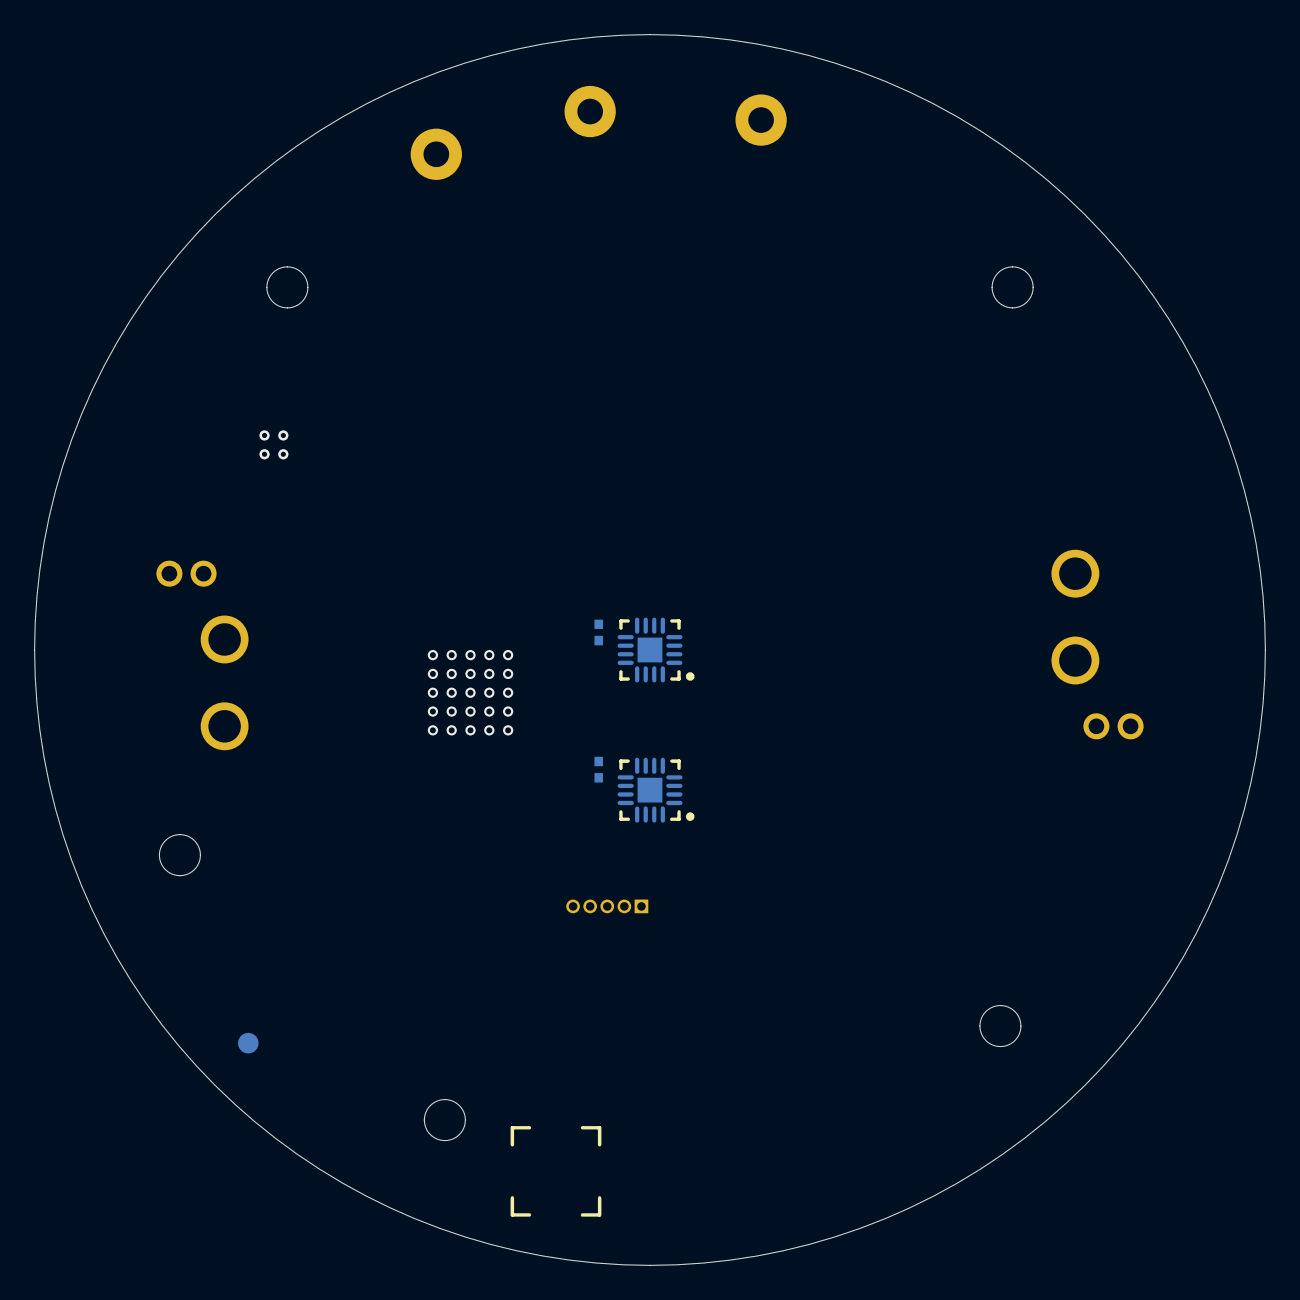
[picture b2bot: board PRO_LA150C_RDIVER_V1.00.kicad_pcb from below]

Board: 4 copper layers, 72.0 x 72.0 mm, 157 parts (6 on the bottom side), 58 nets, no tracks yet.

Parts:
C1, C4, C16, C17, C18, C23, C24, C25, C57, C61, C64: 0402-10pF-50V-5%; C0402_CL_SAMSUNG
C2, C3, C8, C8_1, C19, C20, C21, C22, C28, C45, C46, C52, C56, C58, C60, C62, C63, C65: 0402-100nF-50V-10%; C0402_CL_SAMSUNG
C5, C6, C9: 0603-1uF-25V-10%; C0603_CL_SAMSUNG
C7, C53: 1206-10uF-35V-10%; C1206_CL_SAMSUNG
C10, C11, C12, C13, C14, C15: NC; C0402_CGA_NC_TDK
C26: C0402-100nF; C0402_GRM_MURATA
C30, C51: 0603-100nF-100V-10%; C0603_CL_SAMSUNG
C31, C32, C33, C34, C34_1, C35, C35_1, C35_2, C36, C37, C38, C39, C40, C40_1, C40_1_1, C40_1_2, C40_1_2_1, C41, C41_1, C41_1_1, C41_1_2, C41_1_3, C41_1_3_1, C41_1_3_2, C41_1_3_3, C41_2, C42, C49, C49_1, C49_2, C49_3: 1210-10uF-100V-10%; C1210_SAMSUNG
C43, C44: 1206-2.2nF-630V-5%; C1206_CC_YAGEO
C47, C48, C54: 0805-10uF-25V-10%; C0805_CL_SAMSUNG
C50: 1206-2.2uF-100V-10%; C1206_CL_SAMSUNG
C55, C59: 0603-10uF-10V-10%; C0603_PDC
D1, D3: SOT23/7V or 12V/400W; SOT23_TP
D2: SMB/58V/600W; SMB_PANJIT
Designator4, Designator5: Comment; EMSOP-8_BPS
Designator8, Designator9: Comment; CONN-TH_4P-XT30PW-M
Designator12, Designator13: Comment; QFN-16L_CONNTEK
J2: J_SIP-1X5-1.0mm; DIP-1X5P-1.0-H
L1: 0402-600 Ohms@100MHz; B0402_MURATA
L2: 7.1*6.5*5.0mm/2.2uH/±20%/10.6A; L7.1*6.5*5_TDK
LED1, LED2: XL-1005UGC; LED_0402_XL
MARK1, MARK2: MARK1.2
MOS1, MOS2, MOS3, MOS4, MOS5, MOS6: NMOS/100V/162A/2.6mΩ/DFN5*6; DFN5*6_2_ZMJ
QR2: QR Code-5.1*5.1mm
R1, R1_1, R33, R36, R37, R38, R40, R41, R42, R43, R44, R45: 0402-100K-1%; R0402_RC_YAGEO
R2, R3, R4, R8, R9, R10: 0603-4.7Ω-1%; R0603_RC_YAGEO
R5, R6, R7, R11, R12, R13, R23, R30, R32: 0402-10K-1%; R0402_RC_YAGEO
R14, R15, R16: 0402-150K-1%; R0402_RC_YAGEO
R17, R18, R19, R25, R34, R35: 0402-10KR-1%; R0402_RC_YAGEO
R20, R21, R22: 2512-3mΩ-1%; R2512_WSL_1~49MR_VISHAY
R24, R27: 0402-1.05KΩ-1%; R0402_RC_YAGEO
R26, R28, R29: 0402-20R-1%; R0402_RC_YAGEO
R31: 0402-200K-1%; R0402_RC_YAGEO
TP1, TP2: TP0.8
U2: DRV8300DRGER; VQFN24_TI
U3: UFQFPN48/128KB Flash/32KB SRAM; UFQFPN48_ST
U5: SOT223/5V/1.35A/15V; SOT223_DIODES
U6: SOT-23-5/3.3V/300mA/1.4V～5.5V; SOT-23-5_TI
X1: 8MHz-10pF; Y_8M_MURATA

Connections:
3.3V: C2.1, C3.1, C19.2, C20.1, C21.1, C28.1, C65.1, J2.5, L1.2, R24.1, R25.2, R27.1, R36.2, R37.2, R38.2, U3.1, U3.23, U3.35, U3.48
+3.3V: C59.1, C60.1, U6.5
+5V: C55.1, C56.1, C58.1, U5.3, U6.1, U6.3
+12V: C7.1, C8.1, C46.1, C47.1, C48.1, C53.1, C54.1, L2.2, R30.2, U2.4, U5.2
AD-VBUS: C57.1, R34.2, TP2.0, U3.24
CANFD1-TX: C35_1.2, TP1.0, U3.34
CANH: C1.1, D1.1
CANL: C4.1, D1.2
EGND: C43.2, C44.2
GHA: R2.1, R3.1, R4.1, U2.19
GHB: U2.13, U2.16
GLA: R8.1, R9.1, R10.1, U2.11
GLB: U2.9, U2.10
GND: C1.2, C2.2, C3.2, C4.2, C7.2, C8.2, C19.1, C20.2, C21.2, C22.1, C26.2, C28.2, C30.2, C31.2, C32.2, C33.2, C34.2, C35.2, C36.2, C37.2, C38.2, C39.2, C40.2, C41.2, C42.2, C44.1, C46.2, C47.2, C48.2, C50.2, C51.2, C52.2, C53.2, C54.2, C55.2, C56.2, C57.2, C58.2, C59.2, C60.2, C61.2, C62.2, C63.2, C65.2, D1.3, D2.2, Designator13.5, Designator13.6, Designator13.8, J2.2, R1.1, R23.1, R31.1, R32.1, R35.1, R40.2, R41.2, R42.2, R43.2, R44.2, R45.1, U2.6, U2.7, U2.8, U2.25, U3.49, U5.1, U6.2, U6.4, X1.2
I-A+: C16.1, R14.2, R17.2, U3.9
I-A-: C16.2, C17.2, C18.2, C23.1, C24.1, C25.1, R20.1, R21.1, R22.1, U3.11, U3.13, U3.19
I-B+: C17.1, R15.2, R18.2, U3.15
I-C+: C18.1, R16.2, R19.2, U3.17
IAout: C23.2, U3.10
IBout: C25.2, U3.14
ICout: C24.2, U3.18
LED-CAN: LED2.K, U3.22
LED-RUN: LED1.K, U3.3
LS1: C13.2, MOS4.S, R11.1, R17.1, R20.2
LS2: C14.2, MOS5.S, R12.1, R18.1, R21.2
LS3: C15.2, MOS6.S, R13.1, R19.1, R22.2
MOTA: C5.2, C10.2, C11.2, C12.2, MOS1.S, MOS2.S, MOS3.S, MOS4.D, MOS5.D, MOS6.D, R5.1, R6.1, R7.1, U2.18
NRST: C22.2, R26.2, U3.7
NetC5_1: C5.1, U2.20
NetC6_1: C6.1, U2.17
NetC6_2: C6.2, U2.15
NetC9_1: C9.1, U2.14
NetC9_2: C9.2, U2.12
NetC10_1: C10.1, MOS1.G, R2.2, R5.2
NetC11_1: C11.1, MOS2.G, R3.2, R6.2
NetC12_1: C12.1, MOS3.G, R4.2, R7.2
NetC13_1: C13.1, MOS4.G, R8.2, R11.2
NetC14_1: C14.1, MOS5.G, R9.2, R12.2
NetC15_1: C15.1, MOS6.G, R10.2, R13.2
NetC45_1: C45.1, L2.1
NetC49_2: R30.1, R32.2
NetJ2_1: J2.1, R25.1, R26.1
NetJ2_3: J2.3, R28.1
NetJ2_4: J2.4, R29.1
NetLED1_A: LED1.A, R24.2
NetLED2_A: LED2.A, R27.2
NetR1_2: R1.2, U2.21
NetR33_1: R33.1, R34.1, R35.2
NetR36_1: Designator13.3, Designator13.4, R36.1
NetR38_1: Designator13.9, Designator13.10, R38.1
NetR43_1: Designator13.17, R43.1
OSC-IN: U3.5, X1.1
OSC-OUT: U3.6, X1.3
SWCLK: R28.2, U3.37
SWDIO: R29.2, U3.36
USART3-RX: R23.2, U3.46
VBUS: C30.1, C31.1, C32.1, C33.1, C34.1, C35.1, C36.1, C37.1, C38.1, C39.1, C40.1, C41.1, C42.1, C43.1, C50.1, C51.1, D2.1, MOS1.D, MOS2.D, MOS3.D, R33.2
VREF+: C26.1, L1.1, R14.1, R15.1, R16.1, U3.20, U3.21
